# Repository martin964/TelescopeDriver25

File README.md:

# TelescopeDriver25
Stepper motor controller for telescopes

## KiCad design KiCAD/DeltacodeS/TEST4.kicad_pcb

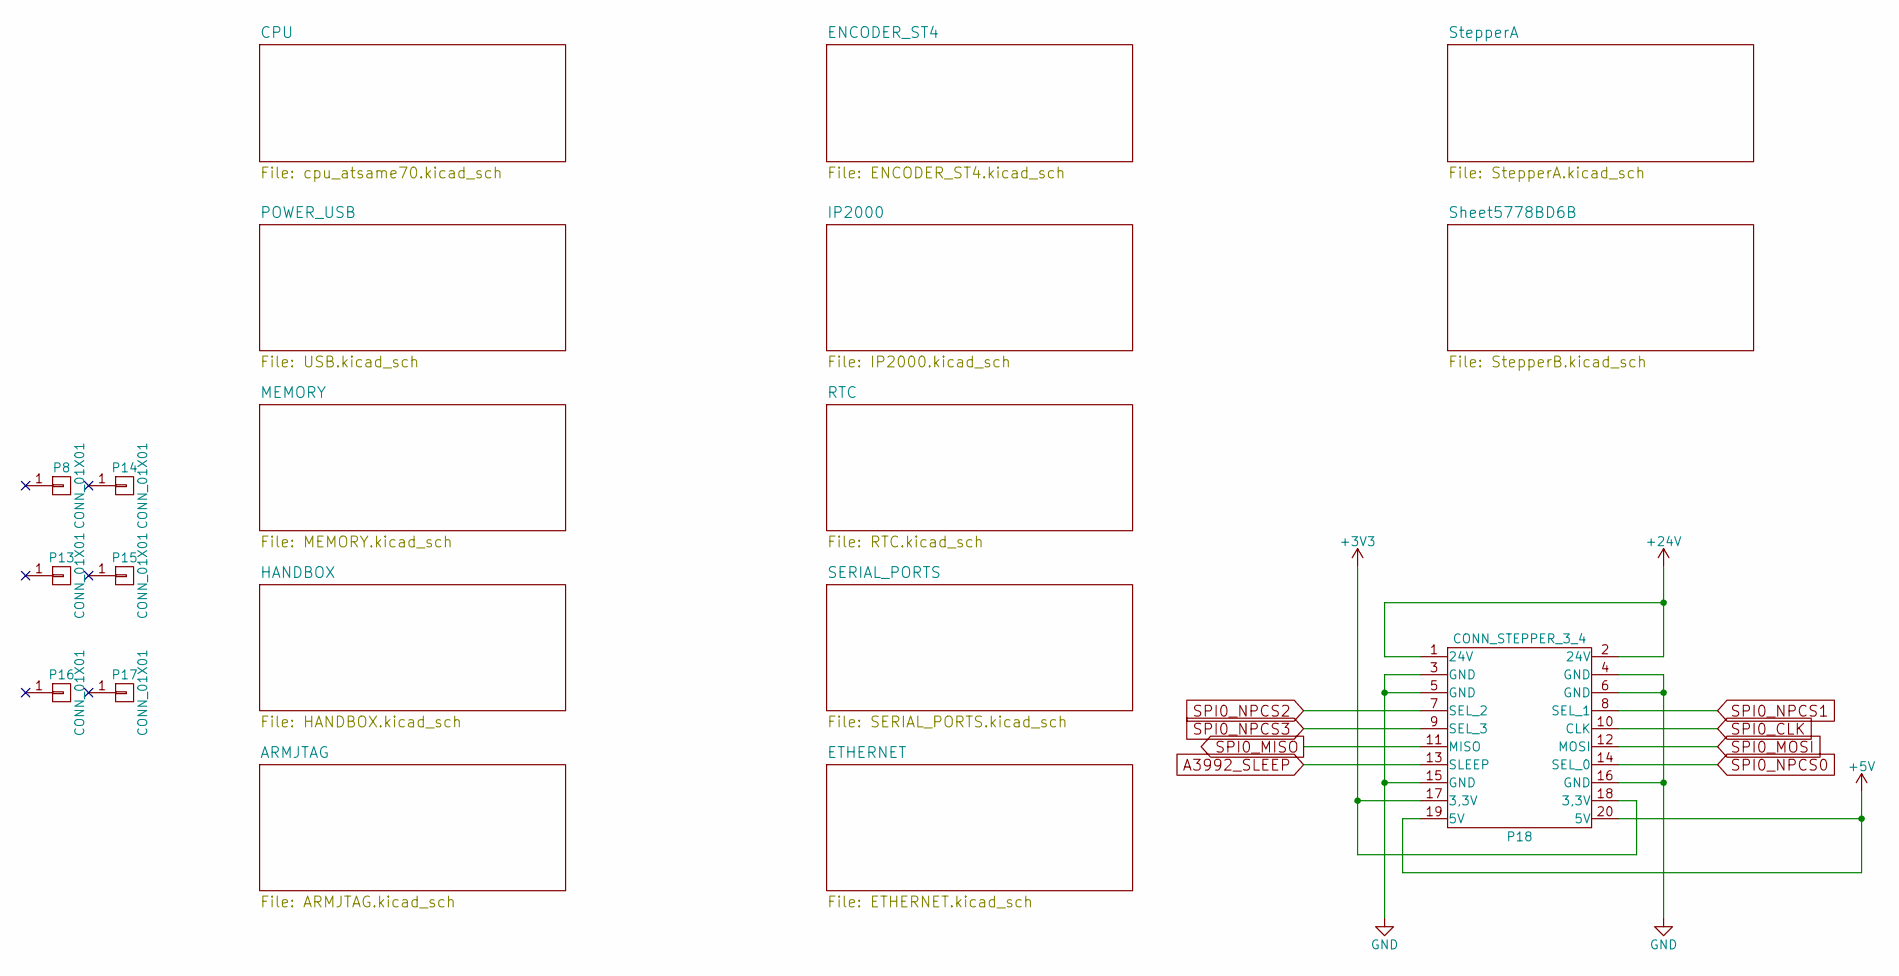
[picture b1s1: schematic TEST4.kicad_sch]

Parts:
P8, P13, P14, P15, P16, P17: CONN_01X01; MountingHole_3.2mm_M3
P18: CONN_STEPPER_3_4; Pin_Header_Straight_2x10

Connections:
+5V: P18.19 (5V), P18.20 (5V); also elsewhere on the board
+24V: P18.1 (24V), P18.2 (24V); also elsewhere on the board
A3992_SLEEP: P18.13 (SLEEP); also elsewhere on the board
GND: P18.3 (GND), P18.4 (GND), P18.5 (GND), P18.6 (GND), P18.15 (GND), P18.16 (GND); also elsewhere on the board
SPI0_CLK: P18.10 (CLK); also elsewhere on the board
SPI0_MISO: P18.11 (MISO); also elsewhere on the board
SPI0_MOSI: P18.12 (MOSI); also elsewhere on the board
SPI0_NPCS0: P18.14 (SEL_0); also elsewhere on the board
SPI0_NPCS1: P18.8 (SEL_1); also elsewhere on the board
SPI0_NPCS2: P18.7 (SEL_2); also elsewhere on the board
SPI0_NPCS3: P18.9 (SEL_3); also elsewhere on the board

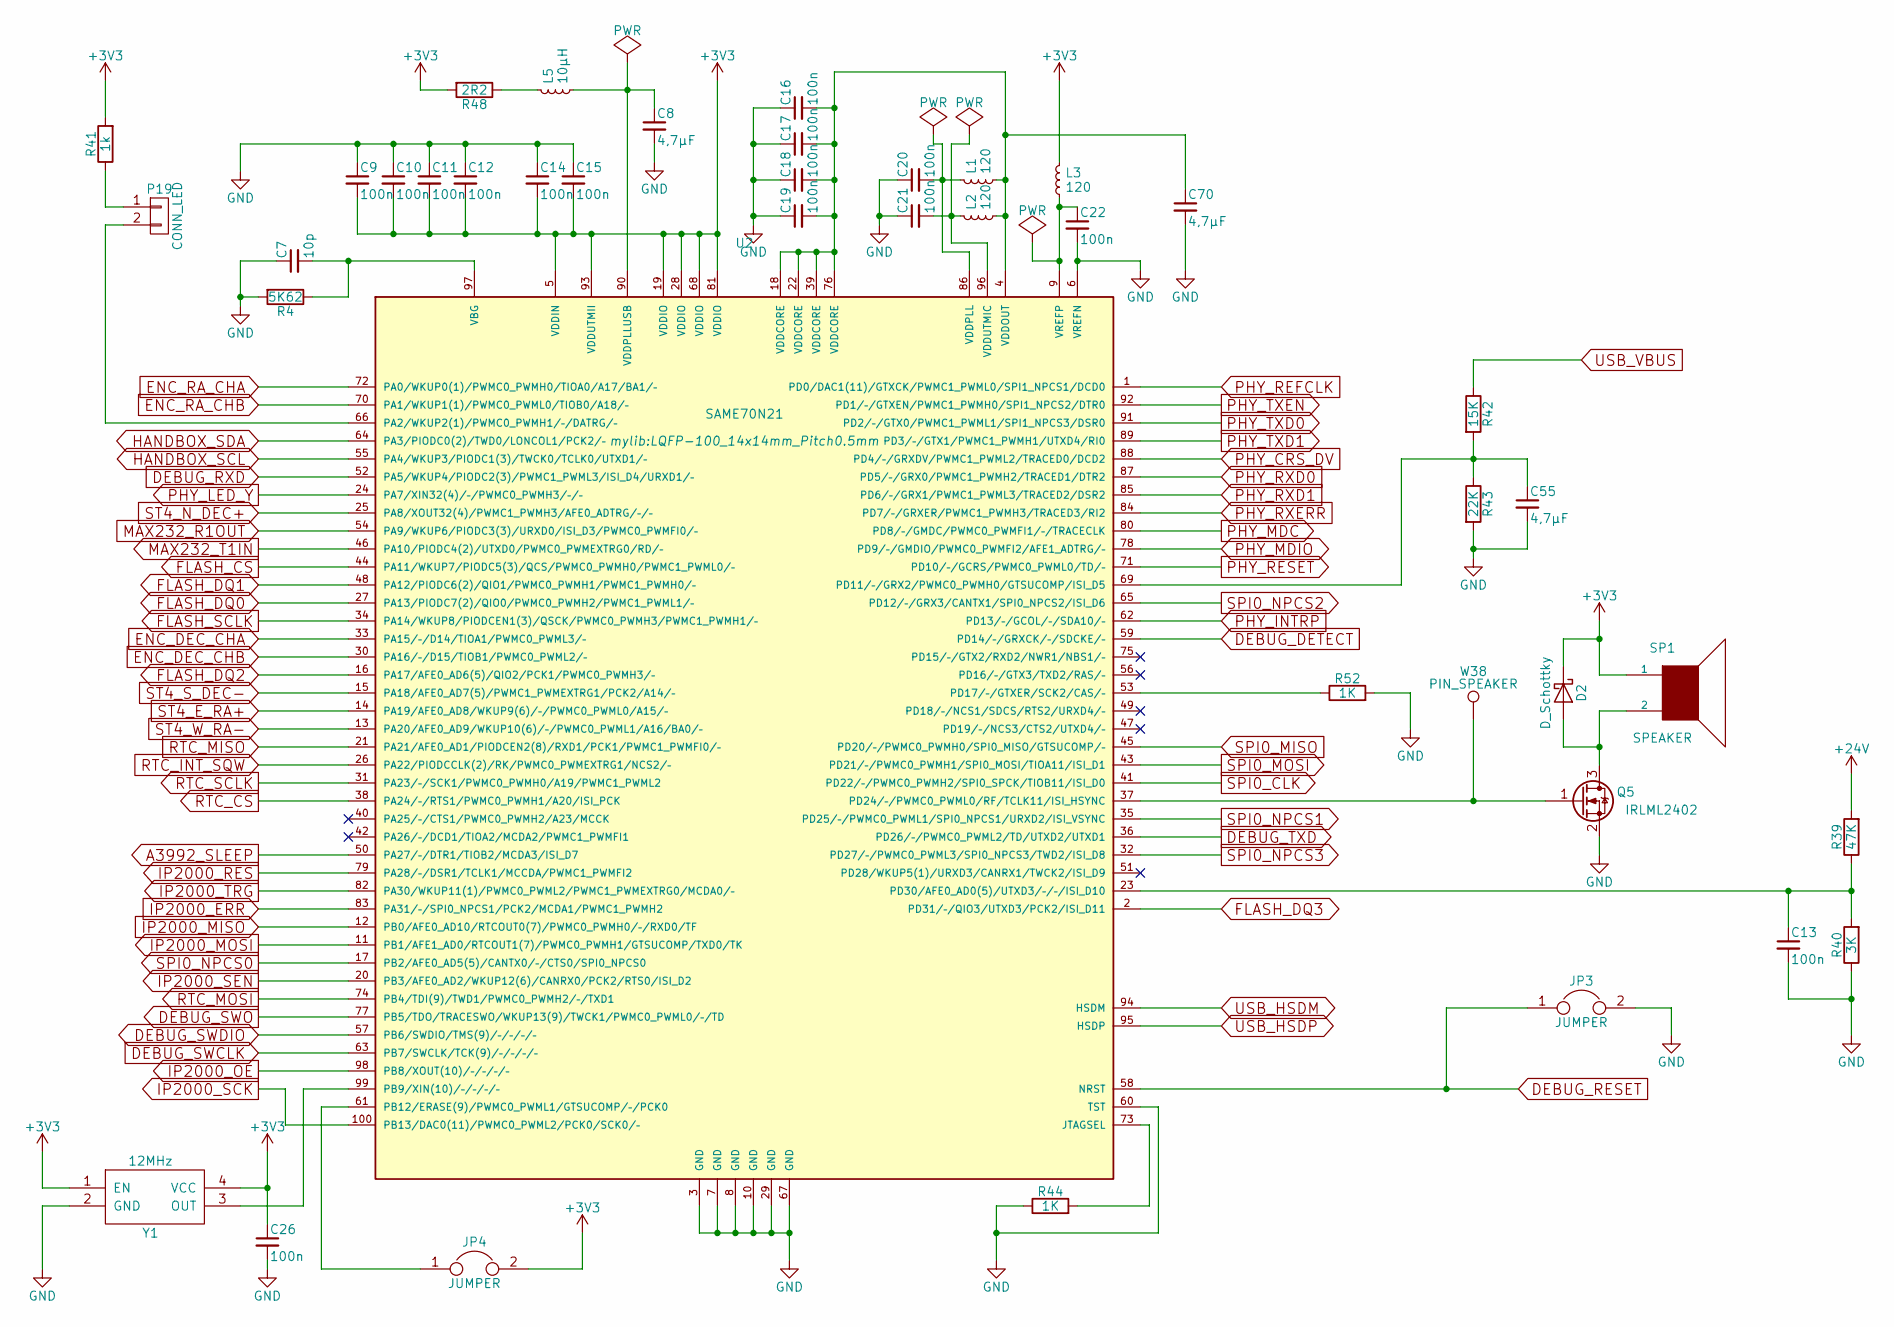
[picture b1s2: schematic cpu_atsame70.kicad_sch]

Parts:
C7: 10p; C_1206
C8, C55, C70: 4,7µF; C_1206
C9, C10, C11, C12, C13, C14, C15, C16, C17, C18, C19, C20, C21, C22, C26: 100n; C_1206
D2: D_Schottky; SMA_Handsoldering
JP3, JP4: JUMPER; Pin_Header_Straight_1x02
L1, L2, L3: 120; C_1207_Reflow
L5: 10µH; L_Chip_1210
P19: CONN_LED; Pin_Header_Straight_1x02
Q5: IRLML2402; SOT-23
R4: 5K62; R_0805
R39: 47K; R_1206
R40: 3K; R_1206
R41: 1k; R_1206
R42: 15K; R_1206
R43: 22K; R_1206
R44, R52: 1K; R_1206
R48: 2R2; R_1206
SP1: SPEAKER; DIGISOUND
U2: SAME70N21; LQFP-100_14x14mm_Pitch0.5mm
W38: PIN_SPEAKER; TestPad_09mmDrill
Y1: 12MHz; TCXO_53

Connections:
+24V: R39.2; also elsewhere on the board
A3992_SLEEP: U2.50 (PA27/–/DTR1/TIOB2/MCDA3/ISI_D7); also elsewhere on the board
DEBUG_DETECT: U2.59 (PD14/–/GRXCK/–/SDCKE/–); also elsewhere on the board
DEBUG_RESET: JP3.1, U2.58 (NRST); also elsewhere on the board
DEBUG_RXD: U2.52 (PA5/WKUP4/PIODC2(3)/PWMC1_PWML3/ISI_D4/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); also elsewhere on the board
DEBUG_SWCLK: U2.63 (PB7/SWCLK/TCK(9)/–/–/–/–); also elsewhere on the board
DEBUG_SWDIO: U2.57 (PB6/SWDIO/TMS(9)/–/–/–/–); also elsewhere on the board
DEBUG_SWO: U2.77 (PB5/TDO/TRACESWO/WKUP13(9)/TWCK1/PWMC0_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); also elsewhere on the board
DEBUG_TXD: U2.36 (PD26/–/PWMC0_PWML2/TD/UTXD2/UTXD1); also elsewhere on the board
ENC_DEC_CHA: U2.33 (PA15/–/D14/TIOA1/PWMC0_PWML3/–); also elsewhere on the board
ENC_DEC_CHB: U2.30 (PA16/–/D15/TIOB1/PWMC0_PWML2/–); also elsewhere on the board
ENC_RA_CHA: U2.72 (PA0/WKUP0(1)/PWMC0_PWMH0/TIOA0/A17/BA1/–); also elsewhere on the board
ENC_RA_CHB: U2.70 (PA1/WKUP1(1)/PWMC0_PWML0/TIOB0/A18/–); also elsewhere on the board
FLASH_CS: U2.44 (PA11/WKUP7/PIODC5(3)/QCS/PWMC0_PWMH0/PW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); also elsewhere on the board
FLASH_DQ0: U2.27 (PA13/PIODC7(2)/QIO0/PWMC0_PWMH2/PWMC1_P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); also elsewhere on the board
FLASH_DQ1: U2.48 (PA12/PIODC6(2)/QIO1/PWMC0_PWMH1/PWMC1_P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); also elsewhere on the board
FLASH_DQ2: U2.16 (PA17/AFE0_AD6(5)/QIO2/PCK1/PWMC0_PWMH3/–); also elsewhere on the board
FLASH_DQ3: U2.2 (PD31/–/QIO3/UTXD3/PCK2/ISI_D11); also elsewhere on the board
FLASH_SCLK: U2.34 (PA14/WKUP8/PIODCEN1(3)/QSCK/PWMC0_PWMH3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); also elsewhere on the board
GND: C7.1, C8.2, C9.1, C10.1, C11.1, C12.1, C13.2, C14.1, C15.1, C16.1, C17.1, C18.1, C19.1, C20.1, C21.1, C22.2, C26.2, C55.2, C70.2, JP3.2, Q5.2 (S), R4.2, R40.1, R43.2, R44.1, R52.2, U2.3 (GND), U2.6 (VREFN), U2.7 (GND), U2.8 (GND), U2.10 (GND), U2.29 (GND), U2.60 (TST), U2.67 (GND), Y1.2 (GND); also elsewhere on the board
HANDBOX_SDA: U2.64 (PA3/PIODC0(2)/TWD0/LONCOL1/PCK2/–); also elsewhere on the board
IP2000_ERR: U2.83 (PA31/–/SPI0_NPCS1/PCK2/MCDA1/PWMC1_PWMH2); also elsewhere on the board
IP2000_MISO: U2.12 (PB0/AFE0_AD10/RTCOUT0(7)/PWMC0_PWMH0/–/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); also elsewhere on the board
IP2000_MOSI: U2.11 (PB1/AFE1_AD0/RTCOUT1(7)/PWMC0_PWMH1/GTS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); also elsewhere on the board
IP2000_OE: U2.98 (PB8/XOUT(10)/–/–/–/–); also elsewhere on the board
IP2000_RES: U2.79 (PA28/–/DSR1/TCLK1/MCCDA/PWMC1_PWMFI2); also elsewhere on the board
IP2000_SCK: U2.100 (PB13/DAC0(11)/PWMC0_PWML2/PCK0/SCK0/–); also elsewhere on the board
IP2000_SEN: U2.20 (PB3/AFE0_AD2/WKUP12(6)/CANRX0/PCK2/RTS0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); also elsewhere on the board
IP2000_TRG: U2.82 (PA30/WKUP11(1)/PWMC0_PWML2/PWMC1_PWMEXT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); also elsewhere on the board
MAX232_R1OUT: U2.54 (PA9/WKUP6/PIODC3(3)/URXD0/ISI_D3/PWMC0_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); also elsewhere on the board
MAX232_T1IN: U2.46 (PA10/PIODC4(2)/UTXD0/PWMC0_PWMEXTRG0/RD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); also elsewhere on the board
unnamed: C7.2, R4.1, U2.97 (VBG)
unnamed: C8.1, L5.2, U2.90 (VDDPLLUSB)
unnamed: C13.1, R39.1, R40.2, U2.23 (PD30/AFE0_AD0(5)/UTXD3/–/–/ISI_D10)
unnamed: C16.2, C17.2, C18.2, C19.2, C70.1, L1.2, L2.2, U2.4 (VDDOUT), U2.18 (VDDCORE), U2.22 (VDDCORE), U2.39 (VDDCORE), U2.76 (VDDCORE)
unnamed: C20.2, L1.1, U2.86 (VDDPLL)
unnamed: C21.2, L2.1, U2.96 (VDDUTMIC)
unnamed: C22.1, L3.2, U2.9 (VREFP)
unnamed: C55.1, R42.2, R43.1, U2.69 (PD11/–/GRX2/PWMC0_PWMH0/GTSUCOMP/ISI_D5)
unnamed: D2.2 (A), Q5.3 (D), SP1.2
unnamed: JP4.1, U2.61 (PB12/ERASE(9)/PWMC0_PWML1/GTSUCOMP/–/PC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)
unnamed: L5.1, R48.1
unnamed: P19.1, R41.1
unnamed: P19.2, U2.66 (PA2/WKUP2(1)/PWMC0_PWMH1/–/DATRG/–)
unnamed: Q5.1 (G), U2.37 (PD24/–/PWMC0_PWML0/RF/TCLK11/ISI_HSYNC), W38.1
unnamed: R44.2, U2.73 (JTAGSEL)
unnamed: R52.1, U2.53 (PD17/–/GTXER/SCK2/CAS/–)
unnamed: U2.99 (PB9/XIN(10)/–/–/–/–), Y1.3 (OUT)
PHY_CRS_DV: U2.88 (PD4/–/GRXDV/PWMC1_PWML2/TRACED0/DCD2); also elsewhere on the board
PHY_INTRP: U2.62 (PD13/–/GCOL/–/SDA10/–); also elsewhere on the board
PHY_LED_Y: U2.24 (PA7/XIN32(4)/–/PWMC0_PWMH3/–/–); also elsewhere on the board
PHY_MDC: U2.80 (PD8/–/GMDC/PWMC0_PWMFI1/–/TRACECLK); also elsewhere on the board
PHY_MDIO: U2.78 (PD9/–/GMDIO/PWMC0_PWMFI2/AFE1_ADTRG/–); also elsewhere on the board
PHY_REFCLK: U2.1 (PD0/DAC1(11)/GTXCK/PWMC1_PWML0/SPI1_NPC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); also elsewhere on the board
PHY_RESET: U2.71 (PD10/–/GCRS/PWMC0_PWML0/TD/–); also elsewhere on the board
PHY_RXD0: U2.87 (PD5/–/GRX0/PWMC1_PWMH2/TRACED1/DTR2); also elsewhere on the board
PHY_RXD1: U2.85 (PD6/–/GRX1/PWMC1_PWML3/TRACED2/DSR2); also elsewhere on the board
PHY_RXERR: U2.84 (PD7/–/GRXER/PWMC1_PWMH3/TRACED3/RI2); also elsewhere on the board
PHY_TXD0: U2.91 (PD2/–/GTX0/PWMC1_PWML1/SPI1_NPCS3/DSR0); also elsewhere on the board
PHY_TXD1: U2.89 (PD3/–/GTX1/PWMC1_PWMH1/UTXD4/RI0); also elsewhere on the board
PHY_TXEN: U2.92 (PD1/–/GTXEN/PWMC1_PWMH0/SPI1_NPCS2/DTR0); also elsewhere on the board
RTC_CS: U2.38 (PA24/–/RTS1/PWMC0_PWMH1/A20/ISI_PCK); also elsewhere on the board
RTC_INT_SQW: U2.26 (PA22/PIODCCLK(2)/RK/PWMC0_PWMEXTRG1/NCS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); also elsewhere on the board
RTC_MISO: U2.21 (PA21/AFE0_AD1/PIODCEN2(8)/RXD1/PCK1/PWM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); also elsewhere on the board
RTC_MOSI: U2.74 (PB4/TDI(9)/TWD1/PWMC0_PWMH2/–/TXD1); also elsewhere on the board
RTC_SCLK: U2.31 (PA23/–/SCK1/PWMC0_PWMH0/A19/PWMC1_PWML2); also elsewhere on the board
SPI0_CLK: U2.41 (PD22/–/PWMC0_PWMH2/SPI0_SPCK/TIOB11/ISI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); also elsewhere on the board
SPI0_MISO: U2.45 (PD20/–/PWMC0_PWMH0/SPI0_MISO/GTSUCOMP/–); also elsewhere on the board
SPI0_MOSI: U2.43 (PD21/–/PWMC0_PWMH1/SPI0_MOSI/TIOA11/ISI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); also elsewhere on the board
SPI0_NPCS0: U2.17 (PB2/AFE0_AD5(5)/CANTX0/–/CTS0/SPI0_NPCS0); also elsewhere on the board
SPI0_NPCS1: U2.35 (PD25/–/PWMC0_PWML1/SPI0_NPCS1/URXD2/ISI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); also elsewhere on the board
SPI0_NPCS2: U2.65 (PD12/–/GRX3/CANTX1/SPI0_NPCS2/ISI_D6); also elsewhere on the board
SPI0_NPCS3: U2.32 (PD27/–/PWMC0_PWML3/SPI0_NPCS3/TWD2/ISI_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); also elsewhere on the board
ST4_E_RA+: U2.14 (PA19/AFE0_AD8/WKUP9(6)/–/PWMC0_PWML0/A1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); also elsewhere on the board
ST4_N_DEC+: U2.25 (PA8/XOUT32(4)/PWMC1_PWMH3/AFE0_ADTRG/–/–); also elsewhere on the board
ST4_S_DEC-: U2.15 (PA18/AFE0_AD7(5)/PWMC1_PWMEXTRG1/PCK2/A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); also elsewhere on the board
ST4_W_RA-: U2.13 (PA20/AFE0_AD9/WKUP10(6)/–/PWMC0_PWML1/A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); also elsewhere on the board
USB_HSDM: U2.94 (HSDM); also elsewhere on the board
USB_HSDP: U2.95 (HSDP); also elsewhere on the board
USB_VBUS: R42.1; also elsewhere on the board

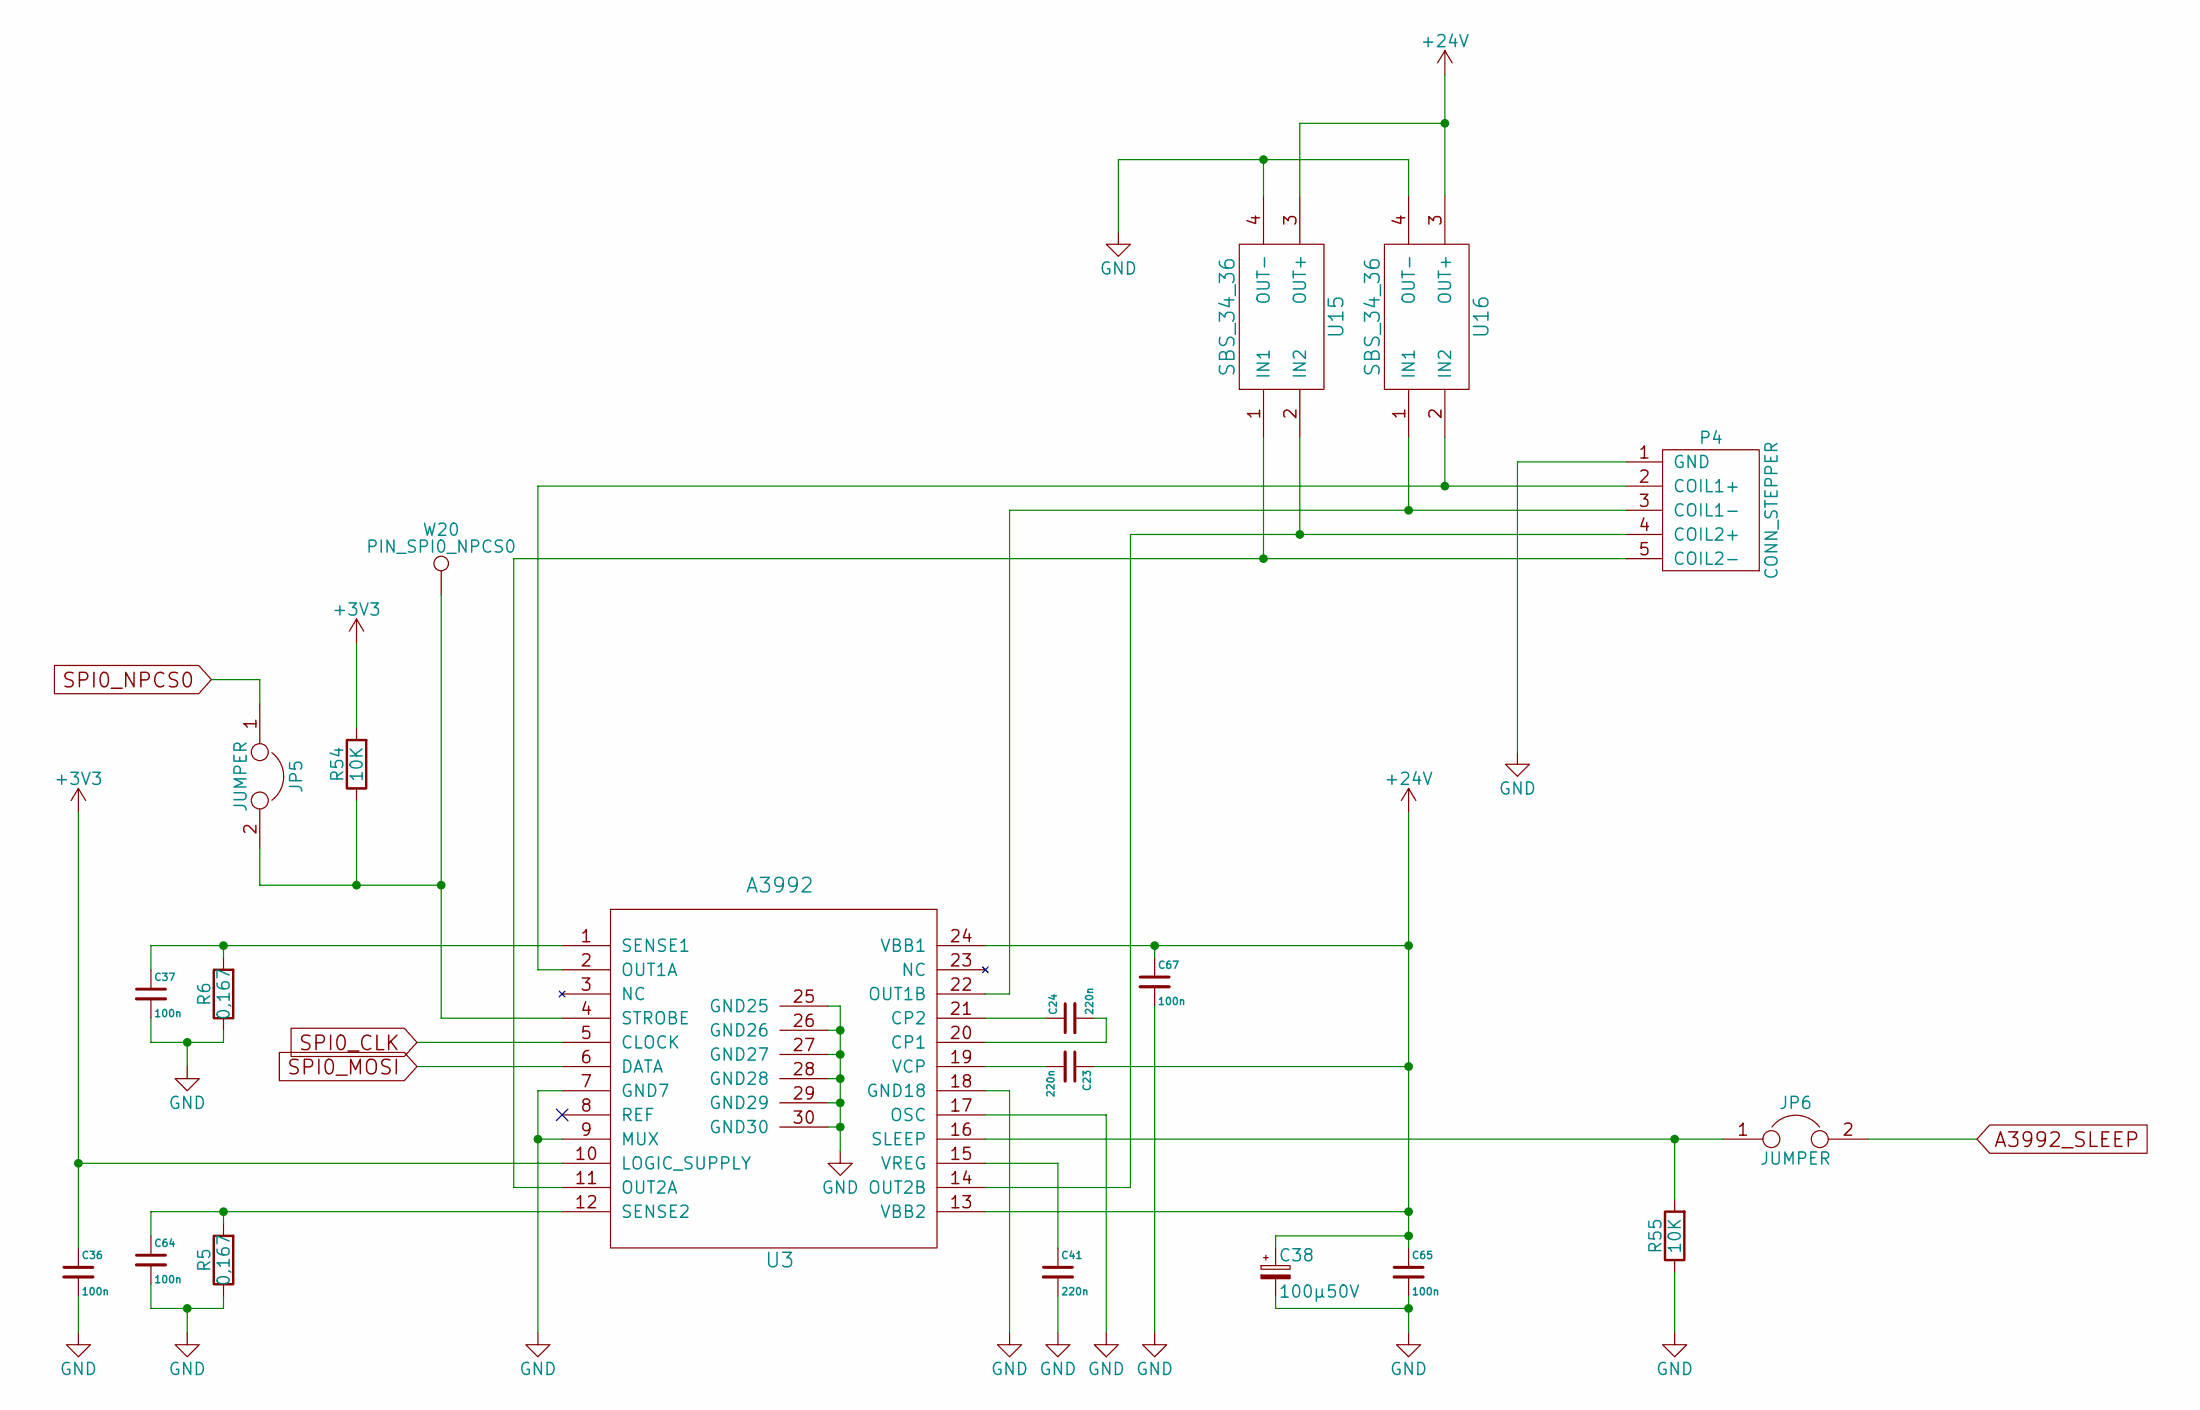
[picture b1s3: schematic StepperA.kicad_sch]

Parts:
C23, C24, C41: 220n; C_1206
C36, C37, C64, C65, C67: 100n; C_1206
C38: 100µ50V; C_Radial_D10_L13_P5
JP5, JP6: JUMPER; Pin_Header_Straight_1x02
P4: CONN_STEPPER; Pin_Header_Straight_LForm_1x05
R5, R6: 0,167; R_2010
R54, R55: 10K; R_1206
U3: A3992; SSOP24_A3992_Pitch0.65mm
U15, U16: SBS_34_36
W20: PIN_SPI0_NPCS0; TestPad_09mmDrill

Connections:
+24V: C23.1, C38.1, C65.1, C67.1, U3.13 (VBB2), U3.24 (VBB1), U15.3 (OUT+), U16.3 (OUT+); also elsewhere on the board
A3992_SLEEP: JP6.2; also elsewhere on the board
GND: C36.2, C37.2, C38.2, C41.2, C64.2, C65.2, C67.2, P4.1 (GND), R5.1, R6.1, R55.1, U3.7 (GND7), U3.9 (MUX), U3.17 (OSC), U3.18 (GND18), U3.25 (GND25), U3.26 (GND26), U3.27 (GND27), U3.28 (GND28), U3.29 (GND29), U3.30 (GND30), U15.4 (OUT-), U16.4 (OUT-); also elsewhere on the board
unnamed: C23.2, U3.19 (VCP)
unnamed: C24.1, U3.21 (CP2)
unnamed: C24.2, U3.20 (CP1)
unnamed: C37.1, R6.2, U3.1 (SENSE1)
unnamed: C41.1, U3.15 (VREG)
unnamed: C64.1, R5.2, U3.12 (SENSE2)
SPI0_CLK: U3.5 (CLOCK); also elsewhere on the board
SPI0_MOSI: U3.6 (DATA); also elsewhere on the board
SPI0_NPCS0: JP5.1; also elsewhere on the board

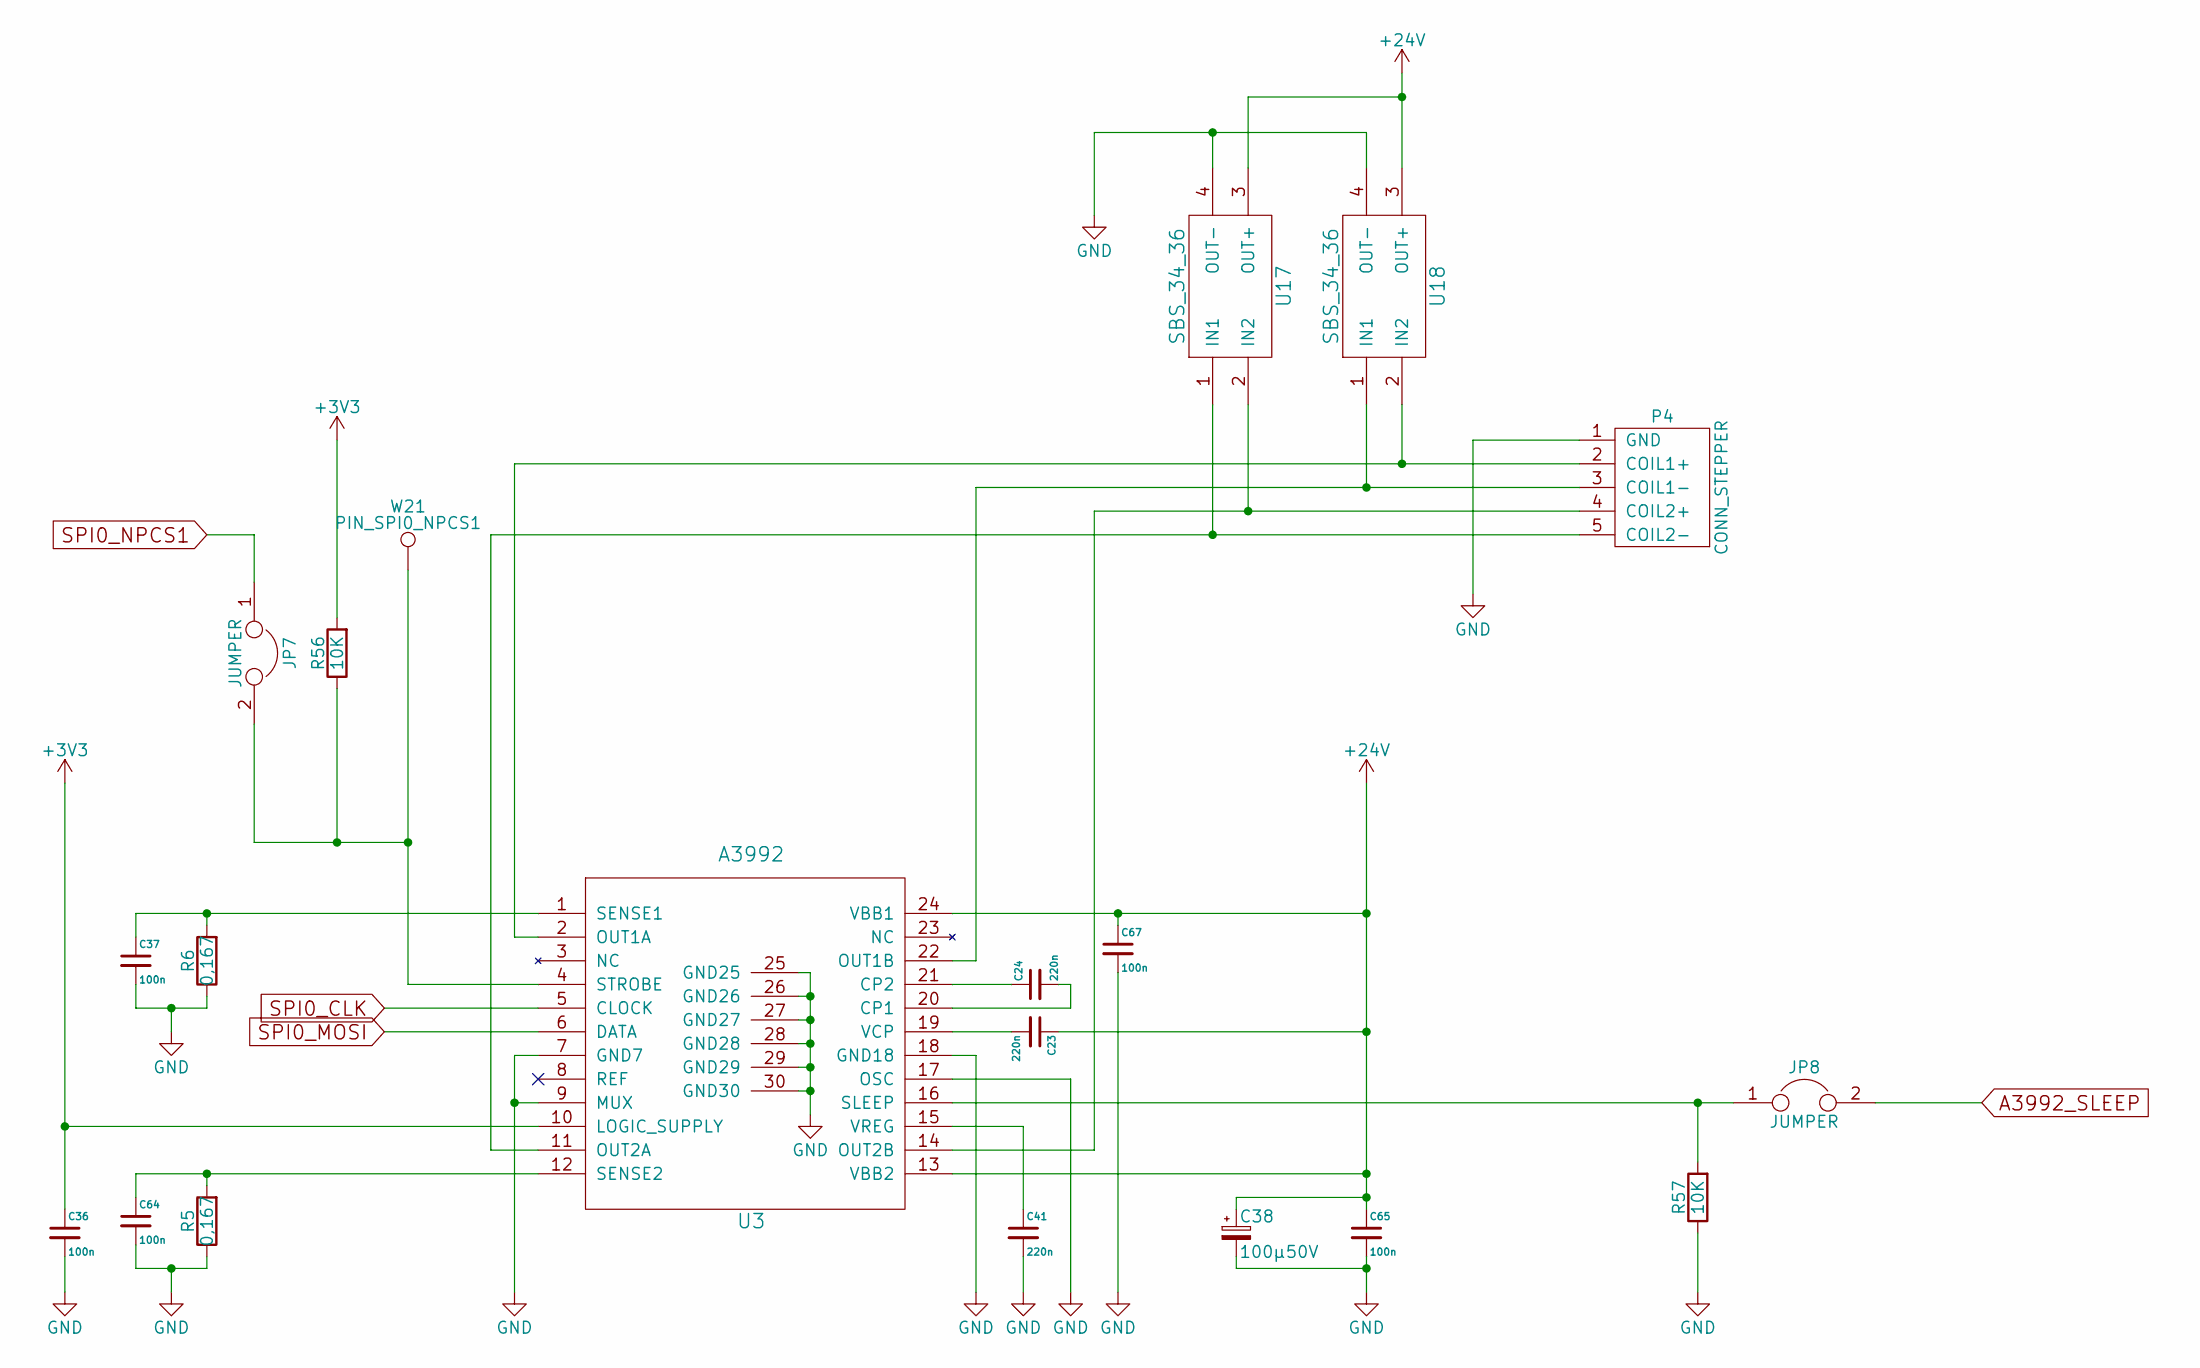
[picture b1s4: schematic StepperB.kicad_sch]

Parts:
C23, C24, C41: 220n; C_1206
C36, C37, C64, C65, C67: 100n; C_1206
C38: 100µ50V; C_Radial_D10_L13_P5
JP7, JP8: JUMPER; Pin_Header_Straight_1x02
P4: CONN_STEPPER; Pin_Header_Straight_LForm_1x05
R5, R6: 0,167; R_2010
R56, R57: 10K; R_1206
U3: A3992; SSOP24_A3992_Pitch0.65mm
U17, U18: SBS_34_36
W21: PIN_SPI0_NPCS1; TestPad_09mmDrill

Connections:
+24V: C23.1, C38.1, C65.1, C67.1, U3.13 (VBB2), U3.24 (VBB1), U17.3 (OUT+), U18.3 (OUT+); also elsewhere on the board
A3992_SLEEP: JP8.2; also elsewhere on the board
GND: C36.2, C37.2, C38.2, C41.2, C64.2, C65.2, C67.2, P4.1 (GND), R5.1, R6.1, R57.1, U3.7 (GND7), U3.9 (MUX), U3.17 (OSC), U3.18 (GND18), U3.25 (GND25), U3.26 (GND26), U3.27 (GND27), U3.28 (GND28), U3.29 (GND29), U3.30 (GND30), U17.4 (OUT-), U18.4 (OUT-); also elsewhere on the board
unnamed: C23.2, U3.19 (VCP)
unnamed: C24.1, U3.21 (CP2)
unnamed: C24.2, U3.20 (CP1)
unnamed: C37.1, R6.2, U3.1 (SENSE1)
unnamed: C41.1, U3.15 (VREG)
unnamed: C64.1, R5.2, U3.12 (SENSE2)
SPI0_CLK: U3.5 (CLOCK); also elsewhere on the board
SPI0_MOSI: U3.6 (DATA); also elsewhere on the board
SPI0_NPCS1: JP7.1; also elsewhere on the board

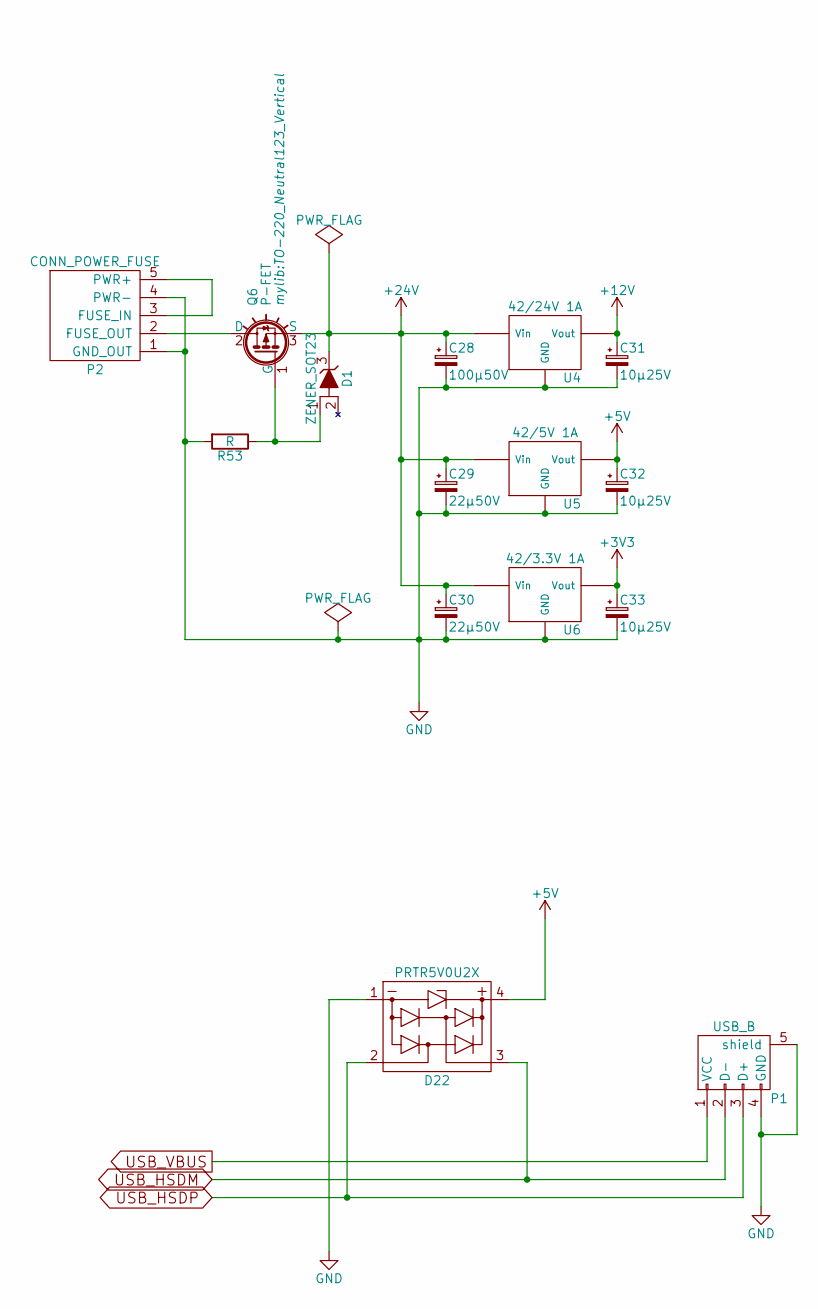
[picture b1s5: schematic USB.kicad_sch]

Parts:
C28: 100µ50V; C_Radial_D10_L13_P5
C29, C30: 22µ50V; C_Radial_D5_L11_P2.5
C31, C32, C33: 10µ25V; C_1206
D1: ZENER_SOT23; SOT-23
D22: PRTR5V0U2X; SOT-143
P1: USB_B; Conn_USBBW_Reichelt
P2: CONN_POWER_FUSE; Pin_Header_Straight_LForm_1x05
Q6: P-FET; TO-220_Neutral123_Vertical
R53: R; R_1206
U4: 42/24V 1A; DCDC-Conv_TRACO_TSR-1
U5: 42/5V 1A; DCDC-Conv_TRACO_TSR-1
U6: 42/3.3V 1A; DCDC-Conv_TRACO_TSR-1

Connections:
+5V: C32.1, D22.4, U5.3 (Vout); also elsewhere on the board
+12V: C31.1, U4.3 (Vout); also elsewhere on the board
+24V: C28.1, C29.1, C30.1, D1.3, Q6.3 (S), U4.1 (Vin), U5.1 (Vin), U6.1 (Vin); also elsewhere on the board
GND: C28.2, C29.2, C30.2, C31.2, C32.2, C33.2, D22.1, P1.4 (GND), P1.5 (shield), P2.1 (GND_OUT), P2.4 (PWR-), R53.2, U4.2 (GND), U5.2 (GND), U6.2 (GND); also elsewhere on the board
unnamed: D1.1 (K), Q6.1 (G), R53.1
unnamed: P2.2 (FUSE_OUT), Q6.2 (D)
unnamed: P2.3 (FUSE_IN), P2.5 (PWR+)
USB_HSDM: D22.3, P1.2 (D-); also elsewhere on the board
USB_HSDP: D22.2, P1.3 (D+); also elsewhere on the board
USB_VBUS: P1.1 (VCC); also elsewhere on the board

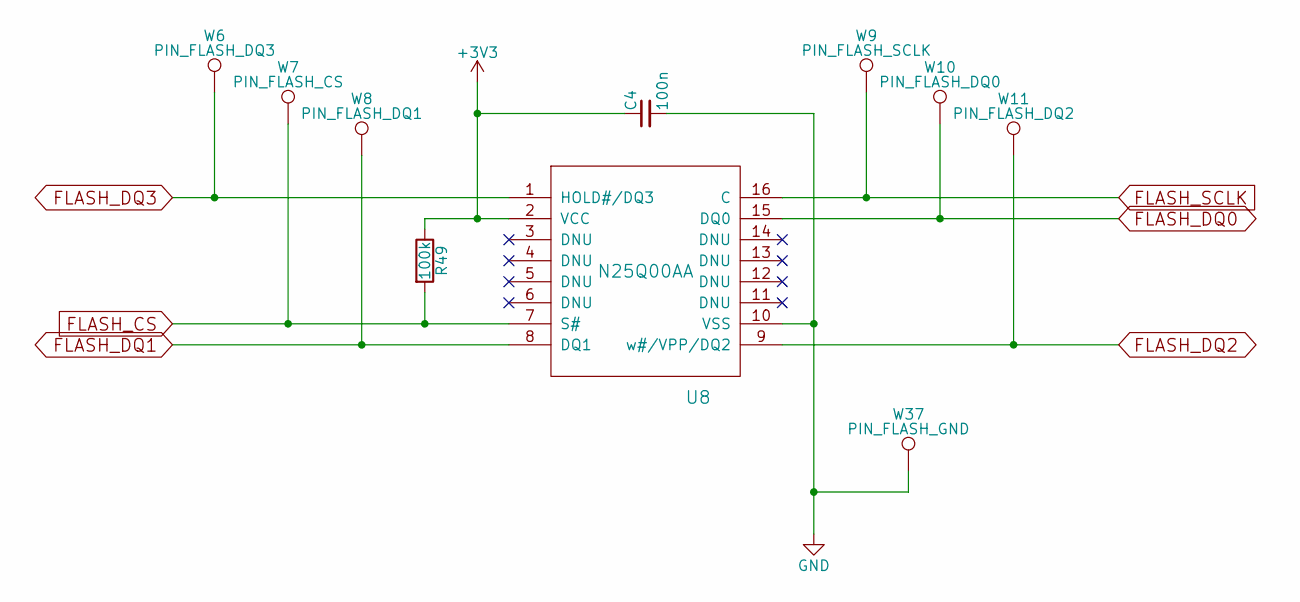
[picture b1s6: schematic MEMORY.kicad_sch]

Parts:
C4: 100n; C_1206
R49: 100k; R_1206
U8: N25Q00AA; SO-16-W
W6: PIN_FLASH_DQ3; TestPad_09mmDrill
W7: PIN_FLASH_CS; TestPad_09mmDrill
W8: PIN_FLASH_DQ1; TestPad_09mmDrill
W9: PIN_FLASH_SCLK; TestPad_09mmDrill
W10: PIN_FLASH_DQ0; TestPad_09mmDrill
W11: PIN_FLASH_DQ2; TestPad_09mmDrill
W37: PIN_FLASH_GND; TestPad_09mmDrill

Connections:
FLASH_CS: R49.2, U8.7 (S#), W7.1; also elsewhere on the board
FLASH_DQ0: U8.15 (DQ0), W10.1; also elsewhere on the board
FLASH_DQ1: U8.8 (DQ1), W8.1; also elsewhere on the board
FLASH_DQ2: U8.9 (w#/VPP/DQ2), W11.1; also elsewhere on the board
FLASH_DQ3: U8.1 (HOLD#/DQ3), W6.1; also elsewhere on the board
FLASH_SCLK: U8.16 (C), W9.1; also elsewhere on the board
GND: C4.2, U8.10 (VSS), W37.1; also elsewhere on the board

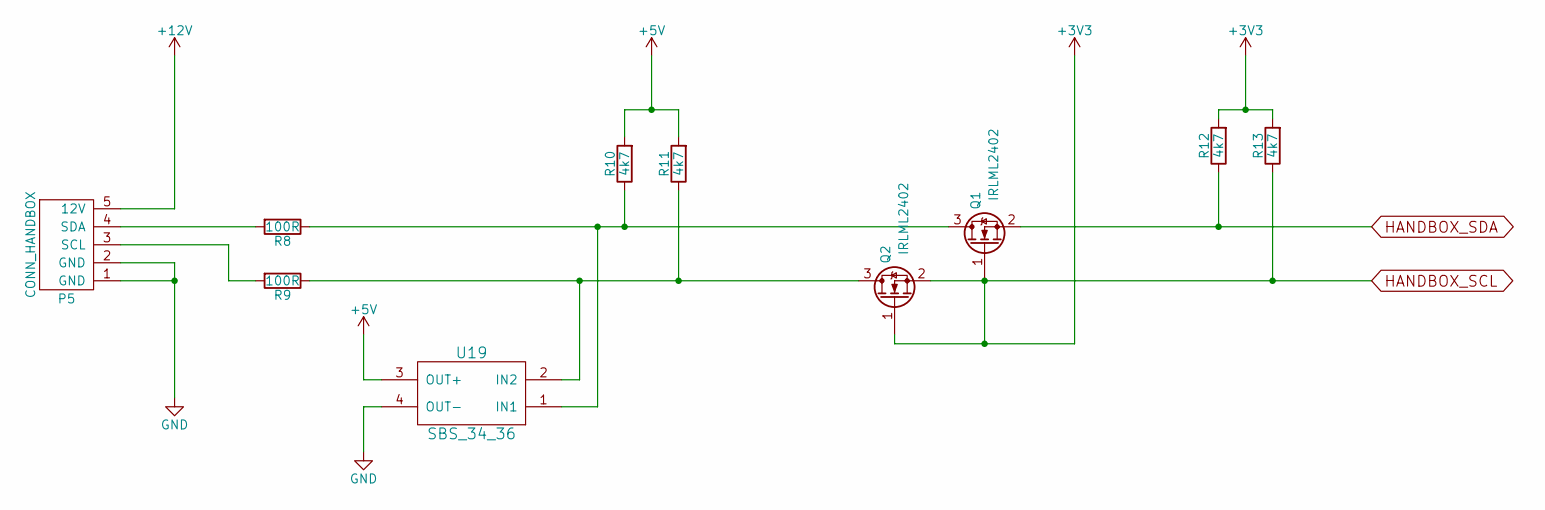
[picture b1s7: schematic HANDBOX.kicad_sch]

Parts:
P5: CONN_HANDBOX; Pin_Header_Straight_LForm_1x05
Q1, Q2: IRLML2402; SOT-23
R8, R9: 100R; R_1206
R10, R11, R12, R13: 4k7; R_1206
U19: SBS_34_36

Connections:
+5V: R10.2, R11.2, U19.3 (OUT+); also elsewhere on the board
+12V: P5.5 (12V); also elsewhere on the board
GND: P5.1 (GND), P5.2 (GND), U19.4 (OUT-); also elsewhere on the board
HANDBOX_SDA: Q1.2 (S), R12.1; also elsewhere on the board
unnamed: P5.3 (SCL), R9.2
unnamed: P5.4 (SDA), R8.2
unnamed: Q1.3 (D), R8.1, R10.1, U19.1 (IN1)
unnamed: Q2.3 (D), R9.1, R11.1, U19.2 (IN2)

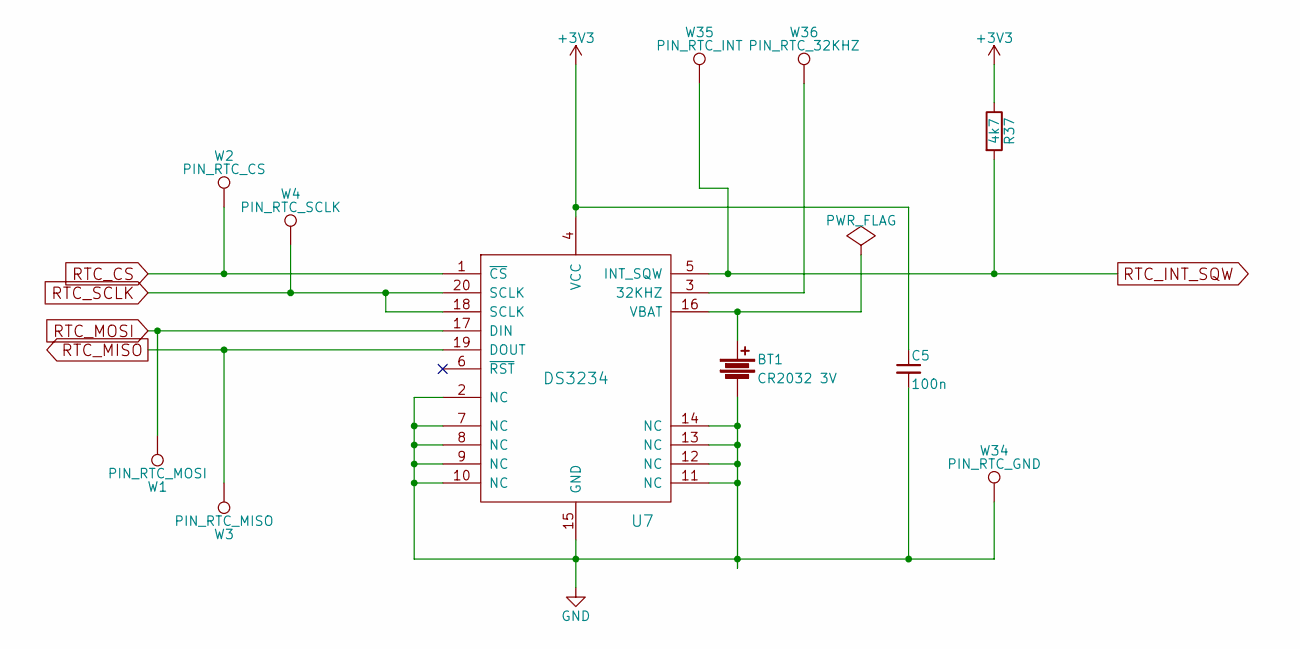
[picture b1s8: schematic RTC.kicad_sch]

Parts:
BT1: CR2032 3V; CR2032H
C5: 100n; C_1206
R37: 4k7; R_1206
U7: DS3234; SOIC-20_7.5x12.8mm_Pitch1.27mm
W1: PIN_RTC_MOSI; TestPad_09mmDrill
W2: PIN_RTC_CS; TestPad_09mmDrill
W3: PIN_RTC_MISO; TestPad_09mmDrill
W4: PIN_RTC_SCLK; TestPad_09mmDrill
W34: PIN_RTC_GND; TestPad_09mmDrill
W35: PIN_RTC_INT; TestPad_09mmDrill
W36: PIN_RTC_32KHZ; TestPad_09mmDrill

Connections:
GND: BT1.2, C5.2, U7.2 (NC), U7.7 (NC), U7.8 (NC), U7.9 (NC), U7.10 (NC), U7.11 (NC), U7.12 (NC), U7.13 (NC), U7.14 (NC), U7.15 (GND), W34.1; also elsewhere on the board
unnamed: BT1.1, U7.16 (VBAT)
unnamed: U7.3 (32KHZ), W36.1
RTC_CS: U7.1 (~CS), W2.1; also elsewhere on the board
RTC_INT_SQW: R37.2, U7.5 (INT_SQW), W35.1; also elsewhere on the board
RTC_MISO: U7.19 (DOUT), W3.1; also elsewhere on the board
RTC_MOSI: U7.17 (DIN), W1.1; also elsewhere on the board
RTC_SCLK: U7.18 (SCLK), U7.20 (SCLK), W4.1; also elsewhere on the board

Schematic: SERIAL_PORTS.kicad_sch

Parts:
C6, C43, C44, C45, C46: 100n; C_1206
JP1, JP2: JUMPER; Pin_Header_Straight_1x02
P12: CONN_DUALRS232; Pin_Header_Straight_LForm_1x05
U9: MAX232; SO-16-N

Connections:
GND: C45.1, C46.2, P12.1 (GND), U9.15 (GND); also elsewhere on the board
MAX232_R1OUT: U9.12 (R1OUT); also elsewhere on the board
MAX232_R2OUT: U9.9 (R2OUT); also elsewhere on the board
MAX232_T1IN: U9.11 (T1IN); also elsewhere on the board
MAX232_T2IN: U9.10 (T2IN); also elsewhere on the board
unnamed: C6.1, U9.1 (C1+)
unnamed: C6.2, U9.3 (C1-)
unnamed: C43.1, U9.4 (C2+)
unnamed: C43.2, U9.5 (C2-)
unnamed: C44.2, U9.2 (V+)
unnamed: C45.2, U9.6 (V-)
unnamed: JP1.1, U9.8 (R2IN)
unnamed: JP1.2, P12.4 (R2)
unnamed: JP2.1, U9.7 (T2OUT)
unnamed: JP2.2, P12.5 (T2)
unnamed: P12.2 (R1), U9.13 (R1IN)
unnamed: P12.3 (T1), U9.14 (T1OUT)
